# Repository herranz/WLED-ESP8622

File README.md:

# WLED-ESP8622
Simplest WLED controller with the ESP8622

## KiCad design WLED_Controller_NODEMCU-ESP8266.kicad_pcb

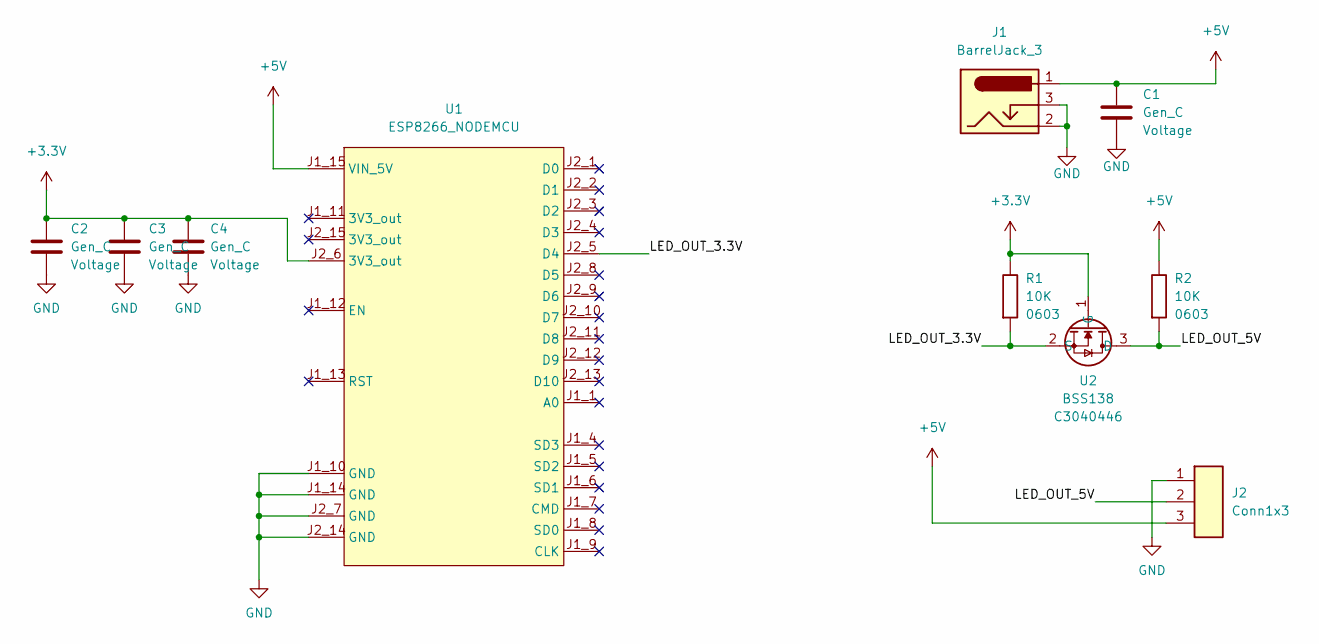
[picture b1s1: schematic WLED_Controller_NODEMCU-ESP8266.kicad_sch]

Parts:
C1: Gen_C; C_0805_2012Metric; Voltage Voltage
C2, C3, C4: Gen_C; C_0603_1608Metric; Voltage Voltage
J1: BarrelJack_3; BarrelJack_GCT_DCJ200-10-A_Horizontal
J2: Conn1x3; TerminalBlock_Phoenix_MKDS-1,5-3-5.08_1x03_P5.08mm_Horizont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
R1, R2: 10K; R_0603_1608Metric
U1: ESP8266_NODEMCU; ESP8266-NodeMCU
U2: BSS138; SOT-23; LCSC C3040446

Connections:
+3.3V: C2.1, C3.1, C4.1, R1.2, U1.J2_6 (3V3_out), U2.1 (G)
+5V: C1.1, J1.1, J2.3, R2.2, U1.J1_15 (VIN_5V)
/LED_OUT_3.3V: R1.1, U1.J2_5 (D4), U2.2 (S)
/LED_OUT_5V: J2.2, R2.1, U2.3 (D)
GND: C1.2, C2.2, C3.2, C4.2, J1.2, J1.3, J2.1, U1.J1_10 (GND), U1.J1_14 (GND), U1.J2_7 (GND), U1.J2_14 (GND)

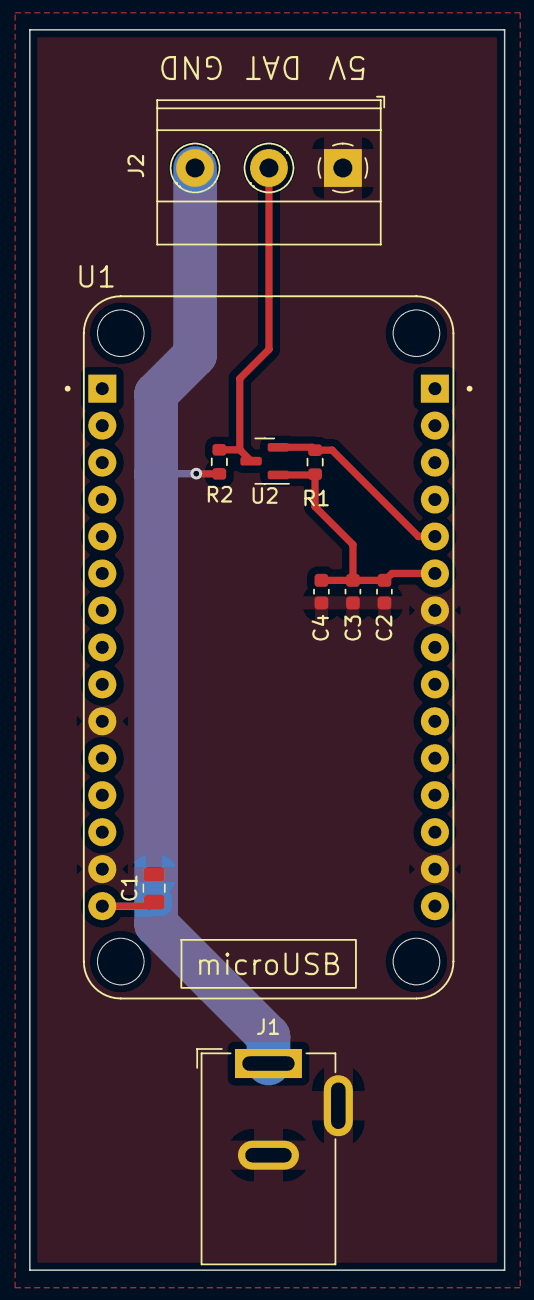
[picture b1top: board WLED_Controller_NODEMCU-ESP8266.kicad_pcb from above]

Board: 2 copper layers, 32.6 x 85.2 mm, 10 parts (0 on the bottom side), 5 nets.

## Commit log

2022-12-12 Inicio proyecto
